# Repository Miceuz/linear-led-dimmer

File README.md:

# linear-led-dimmer
A linear dimmer for 6W - 12W LED pannels.

This dimmer has to burn some power in order to dimm leds for custom made LED pannel used in cinema settings. We need to resort to crude linear dimming in order to avoid any kind of flicker on camera.

More info and eye candy here:

* 
* 
* 
* 
*

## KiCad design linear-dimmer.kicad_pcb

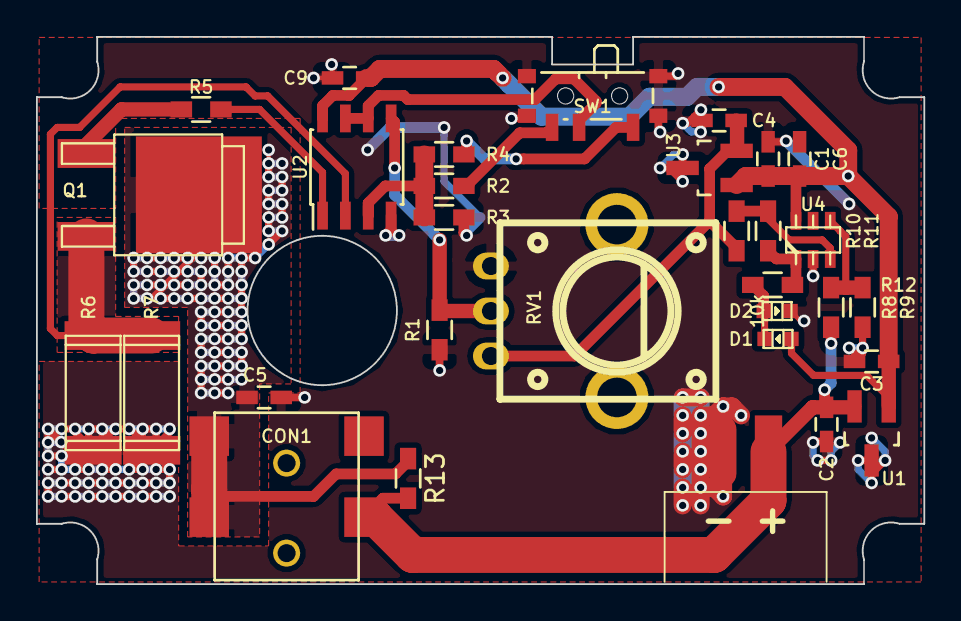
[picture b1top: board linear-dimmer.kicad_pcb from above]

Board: 2 copper layers, 49.3 x 30.4 mm, 31 parts (0 on the bottom side), 17 nets.

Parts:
C1, C2, C3, C4, C5, C6, C9: 1u; C_0603_HandSoldering
CON1: BARREL_JACK; WURTH694102107102
D1: BLUE; Led_0603
D2: RED; Led_0603
P1: POWER; pin_socket_2
Q1: BUK6207-55C; d-pak
R1, R13: 2k; R_0603_HandSoldering
R2: 17.4k; R_0603_HandSoldering
R3, R9, R10: 10k; R_0603_HandSoldering
R4: 45.3k; R_0603_HandSoldering
R5, R12: 220; R_0603_HandSoldering
R6, R7: 0R5; r_2512
R8: 78.7k; R_0603_HandSoldering
R11: 1M; R_0603_HandSoldering
RV1: 10k; trimmer_alps-rk09k1130ah1
SW1: Switch_SPDT_x2; SW_SPDT_PCM12
U1: LM78L05ACZ; SOT-23_Handsoldering
U2: MCP6072; SOIC-8_3.9x4.9mm_Pitch1.27mm
U3: REF3012; SOT-23_Handsoldering
U4: MCP65R41T; sot23-6

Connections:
+1.2V: C4.1, R10.1, RV1.3, U3.2
+5V: C1.1, C3.1, C6.1, C9.1, D1.1, U1.1, U2.8, U3.1, U4.6
/OUTPUT: C5.1, CON1.1, Q1.2, R13.2
GND: C1.2, C2.2, C3.2, C4.2, C5.2, C6.2, C9.2, D2.2, P1.2, R1.2, R3.2, R6.2, R7.2, R9.2, RV1.1, U1.3, U2.4, U3.3, U4.2
unnamed: D1.2, D2.1, R12.2
unnamed: Q1.1, R5.2
unnamed: Q1.3, R6.1, R7.1, U2.2
unnamed: R1.1, RV1.2, U2.5
unnamed: R2.1, R3.1, R4.1, U2.3
unnamed: R2.2, SW1.3
unnamed: R4.2, SW1.1
unnamed: R5.1, U2.1
unnamed: R8.2, R9.1, U4.4
unnamed: R10.2, R11.1, U4.3
unnamed: R11.2, R12.1, U4.1
unnamed: SW1.2, U2.6, U2.7
VCC: C2.1, CON1.2, P1.1, R8.1, R13.1, U1.2

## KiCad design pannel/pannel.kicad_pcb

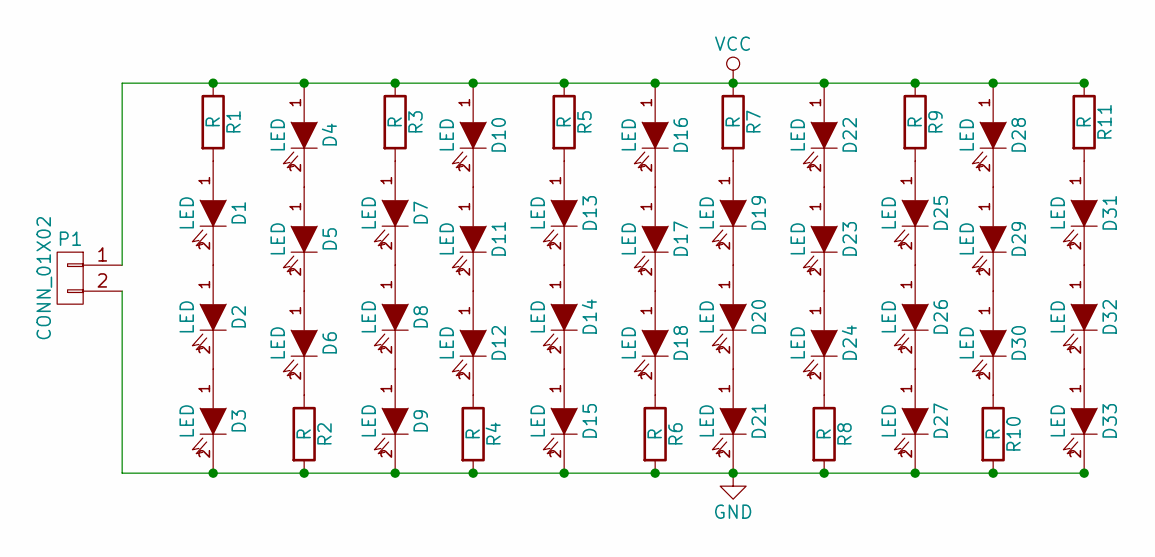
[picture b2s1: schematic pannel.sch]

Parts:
D1, D2, D3, D4, D5, D6, D7, D8, D9, D10, D11, D12, D13, D14, D15, D16, D17, D18, D19, D20, D21, D22, D23, D24, D25, D26, D27, D28, D29, D30, D31, D32, D33: LED; LED5730; PartNo ?
P1: CONN_01X02; Pin_Header_Angled_1x02; PartNo ?
R1, R2, R3, R4, R5, R6, R7, R8, R9, R10, R11: R; R_2010; PartNo MC2010W2F330LT4E

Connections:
GND: D3.2 (K), D9.2 (K), D15.2 (K), D21.2 (K), D27.2 (K), D33.2 (K), P1.2, R2.2, R4.2, R6.2, R8.2, R10.2
unnamed: D1.1 (A), R1.2
unnamed: D1.2 (K), D2.1 (A)
unnamed: D2.2 (K), D3.1 (A)
unnamed: D4.2 (K), D5.1 (A)
unnamed: D5.2 (K), D6.1 (A)
unnamed: D6.2 (K), R2.1
unnamed: D7.1 (A), R3.2
unnamed: D7.2 (K), D8.1 (A)
unnamed: D8.2 (K), D9.1 (A)
unnamed: D10.2 (K), D11.1 (A)
unnamed: D11.2 (K), D12.1 (A)
unnamed: D12.2 (K), R4.1
unnamed: D13.1 (A), R5.2
unnamed: D13.2 (K), D14.1 (A)
unnamed: D14.2 (K), D15.1 (A)
unnamed: D16.2 (K), D17.1 (A)
unnamed: D17.2 (K), D18.1 (A)
unnamed: D18.2 (K), R6.1
unnamed: D19.1 (A), R7.2
unnamed: D19.2 (K), D20.1 (A)
unnamed: D20.2 (K), D21.1 (A)
unnamed: D22.2 (K), D23.1 (A)
unnamed: D23.2 (K), D24.1 (A)
unnamed: D24.2 (K), R8.1
unnamed: D25.1 (A), R9.2
unnamed: D25.2 (K), D26.1 (A)
unnamed: D26.2 (K), D27.1 (A)
unnamed: D28.2 (K), D29.1 (A)
unnamed: D29.2 (K), D30.1 (A)
unnamed: D30.2 (K), R10.1
unnamed: D31.1 (A), R11.2
unnamed: D31.2 (K), D32.1 (A)
unnamed: D32.2 (K), D33.1 (A)
VCC: D4.1 (A), D10.1 (A), D16.1 (A), D22.1 (A), D28.1 (A), P1.1, R1.1, R3.1, R5.1, R7.1, R9.1, R11.1

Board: 2 copper layers, 45 parts (0 on the bottom side), 35 nets, no tracks yet.

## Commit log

2015-07-08 initial
2015-07-08 Add LED, shuffle stuff around
2015-07-08 Shuffle stuff around, hide footprints in schematics
2015-07-09 Shuffle stuff around, generate gerbers
2015-07-12 Add bom
2015-07-12 Set some resistor values and FarnellIDs
2015-07-12 Some trivial changes
2015-08-31 Add source
2015-08-31 Add datasheet for the best diodes
2015-08-31 Add a switcher simulation - this one does not work good, but anyway, have it here
2015-08-31 Add a simulation of nonlinear pot
2015-08-31 Redraw schematics with just a pot and an opamp current source
2015-09-20 Add buffer opamp, choose a different opamp, redraw the PCB with dumb linead current source
2015-10-06 Ready to send to PCB house
2015-10-06 Last stray save
2015-10-22 Update the value for shunt resistors, recalculate divider values accordingly
2015-10-22 Put the power on led to comparator so that blue changes to red on battery low
2015-10-22 Schematic changes after new kicad version
2015-10-22 Stray fogotten edit to bom
2015-10-24 Flip comparator inputs, flip potentiometer
2015-10-24 Add a dummy load resistor so that opamp will be forced to swing the output down at the lowest current setting turning the LEDs off
2015-10-24 Put load to the proper place in schematics
2015-10-24 Implement changes in PCB
2015-11-16 Add 3d model for the switch
2015-11-16 Add amperage markings
2015-12-02 Generate gerbers for the fixed version of linear dimmer
2015-12-02 Fix version number on silkscreen
2015-12-02 Add LED pannel for aluminium PCB
2015-12-02 Add the beginning of spec/marketing material
2015-12-14 Swap silkscreen markings of the output current switch
2015-12-14 Add a resistor for the blue led to embarass less
2017-07-19 all the rest
